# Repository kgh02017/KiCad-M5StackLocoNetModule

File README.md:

# KiCad-M5StackLocoNetModule

KiCad6 project files for M5Stack LocoNet Module

## Description

This repositorhy contains KiCad6 project files for M5Stack LocoNet Module.
M5Stack LocoNet Module has a LocoNet interface to send and receive LocoNet messages.

### Artifacts

- [Schematic](./artifacts/M5StackLocoNetModule-schematic.pdf)
- [BOM](https://htmlview.glitch.me/?https://github.com/kgh02017/KiCad-M5StackLocoNetModule/blob/main/project/M5StackLocoNetModule/bom/M5StackLocoNetModule.html)

## Arthor

Taku Izumi

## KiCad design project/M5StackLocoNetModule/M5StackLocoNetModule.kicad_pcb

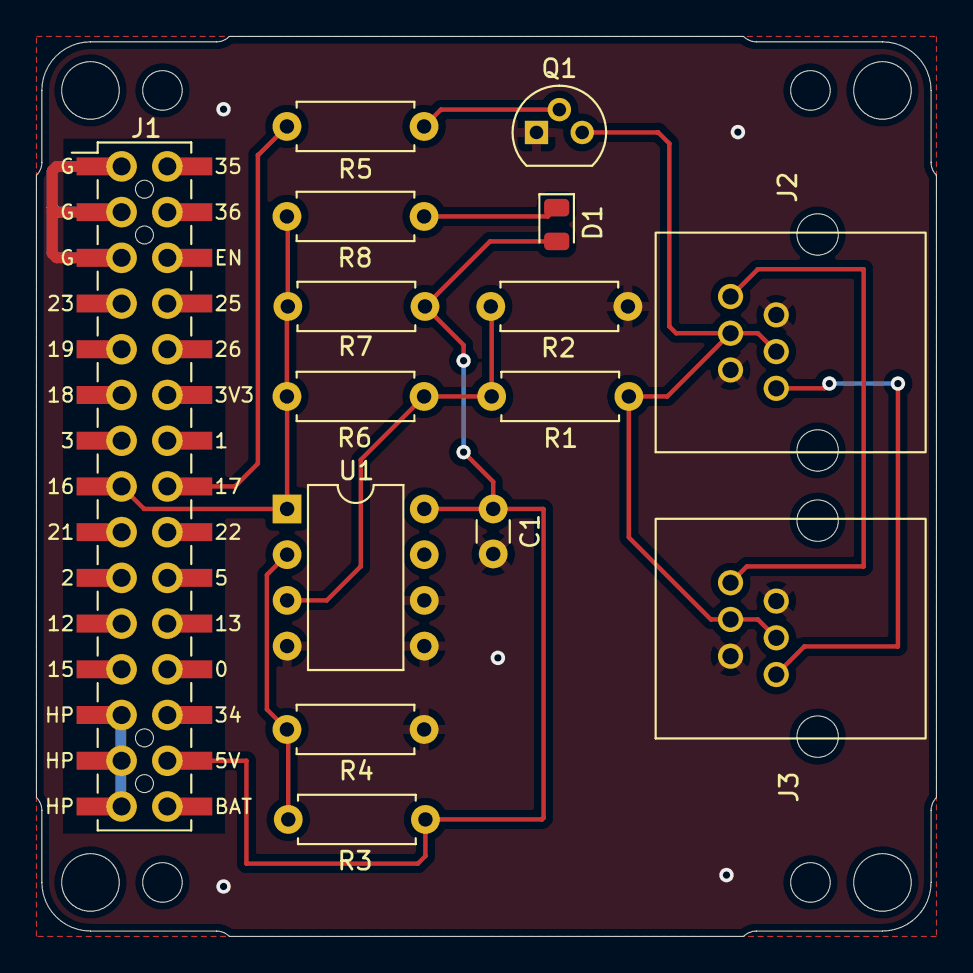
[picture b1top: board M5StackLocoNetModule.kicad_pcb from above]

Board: 2 copper layers, 50.0 x 50.0 mm, 23 parts (0 on the bottom side), 12 nets.

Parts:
C1: 0.1u; C_Disc_D3.0mm_W1.6mm_P2.50mm
D1: LED; LED_0805_2012Metric
H1, H2, H3, H4: MountingHole; BF@MountingHole_3.2mm_M3
H5, H6, H7, H8: MountingHole; BF@MountingHole_2.2mm_M2
J1: M-BUS; BF@M5Stack_MBUS
J2, J3: RJ12; RJ12_6P6C_Jack
Q1: 2N3904; TO-92
R1: 47k; R_Axial_DIN0207_L6.3mm_D2.5mm_P7.62mm_Horizontal
R2: 150k; R_Axial_DIN0207_L6.3mm_D2.5mm_P7.62mm_Horizontal
R3: 27k; R_Axial_DIN0207_L6.3mm_D2.5mm_P7.62mm_Horizontal
R4: 39k; R_Axial_DIN0207_L6.3mm_D2.5mm_P7.62mm_Horizontal
R5: 4.7K; R_Axial_DIN0207_L6.3mm_D2.5mm_P7.62mm_Horizontal
R6: 240k; R_Axial_DIN0207_L6.3mm_D2.5mm_P7.62mm_Horizontal
R7: 1k; R_Axial_DIN0207_L6.3mm_D2.5mm_P7.62mm_Horizontal
R8: 470; R_Axial_DIN0207_L6.3mm_D2.5mm_P7.62mm_Horizontal
U1: LM393; DIP-8_W7.62mm

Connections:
+5V: C1.1, D1.2 (A), J1.27, R3.1, R7.1, U1.8 (V+)
GND: C1.2, J1.2, J1.4, J1.6, J2.2, J2.5, J3.2, J3.5, Q1.1 (E), R2.2, R4.2, U1.4 (V-), U1.5 (+), U1.6 (-)
unnamed: D1.1 (K), R8.1
unnamed: J2.1, J3.1
unnamed: J2.3, J2.4, J3.3, J3.4, Q1.3 (C), R1.1
unnamed: J2.6, J3.6
unnamed: Q1.2 (B), R5.1
unnamed: R1.2, R2.1, R6.1, U1.3 (+)
unnamed: R3.2, R4.1, U1.2 (-)
RX: J1.16, R6.2, R7.2, R8.2, U1.1
TX: J1.15, R5.2
VBUS: J1.26, J1.28, J1.30

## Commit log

2022-12-11 Add KiCad6 project files for M5StackLocoNetModule
